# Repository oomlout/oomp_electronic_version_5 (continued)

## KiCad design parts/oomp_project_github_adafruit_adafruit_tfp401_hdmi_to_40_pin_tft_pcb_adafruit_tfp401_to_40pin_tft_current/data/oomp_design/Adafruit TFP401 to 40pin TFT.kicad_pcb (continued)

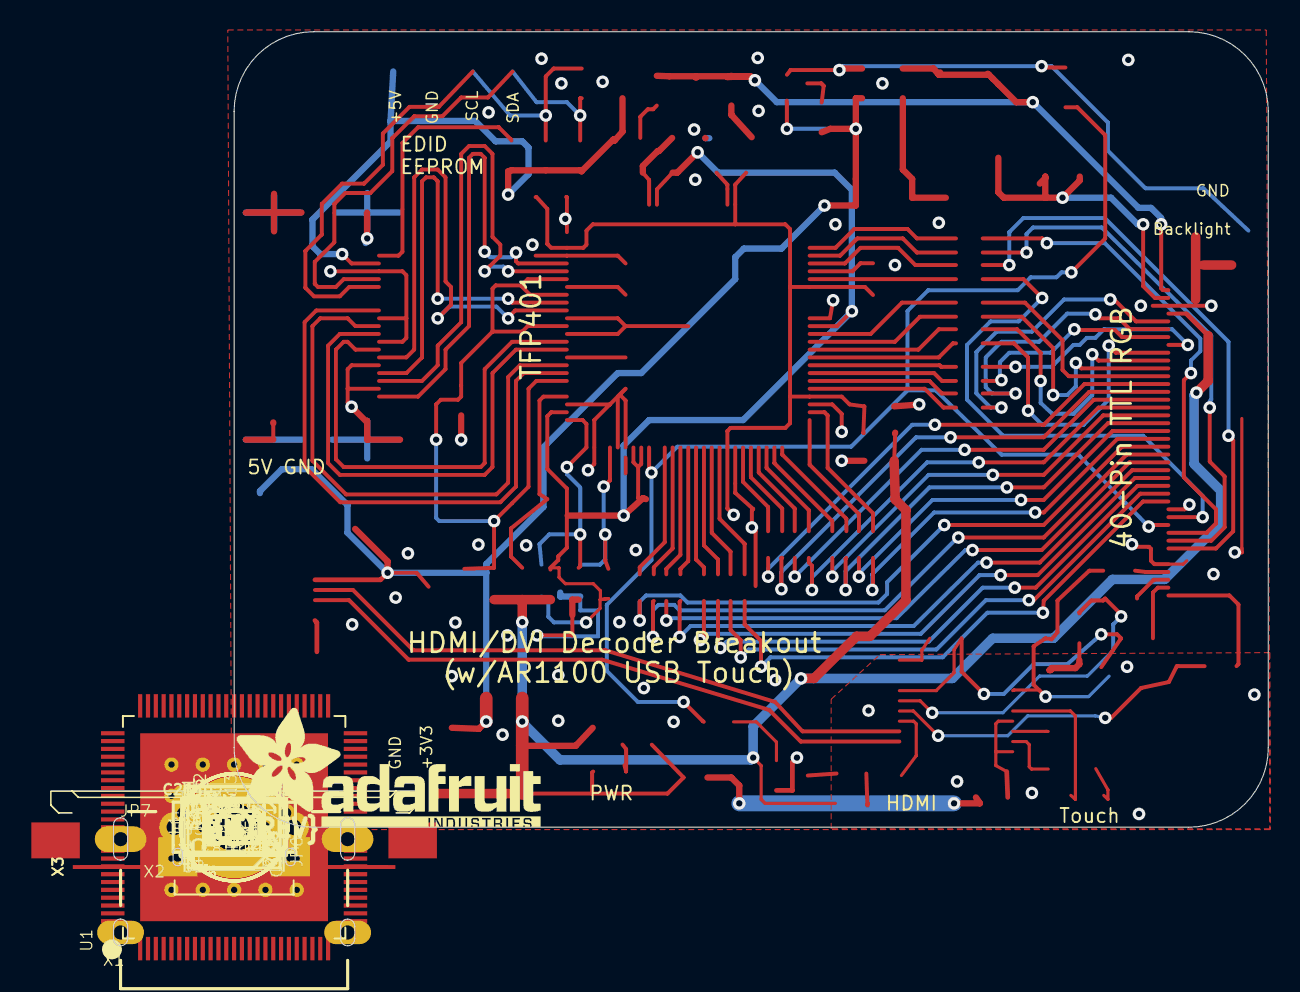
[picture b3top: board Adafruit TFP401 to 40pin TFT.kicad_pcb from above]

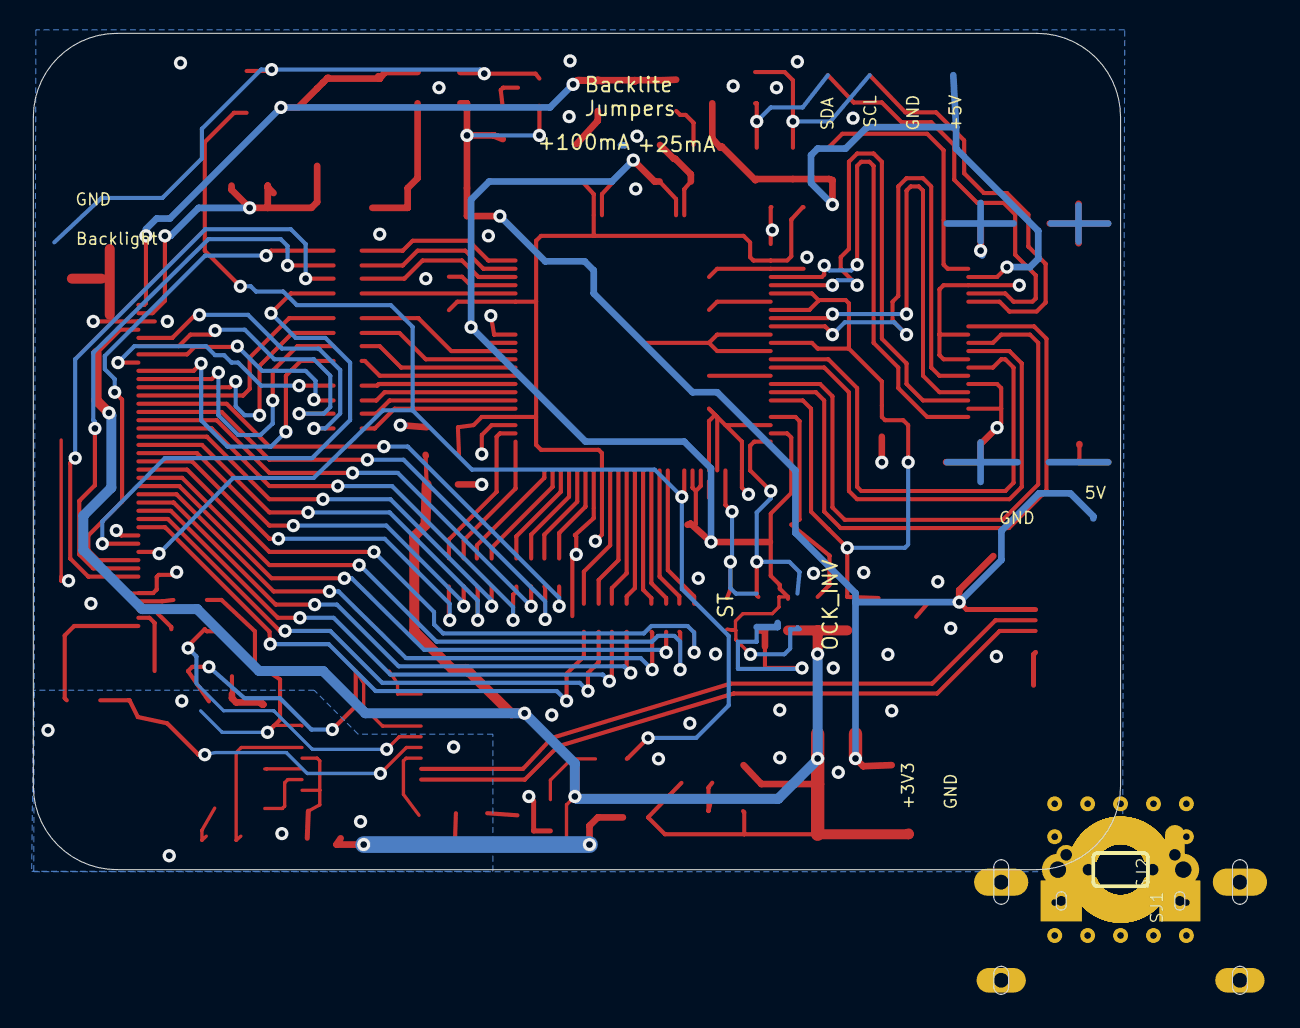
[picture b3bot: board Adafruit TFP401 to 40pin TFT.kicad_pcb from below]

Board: 2 copper layers, 66.0 x 50.8 mm, 92 parts (2 on the bottom side), 107 nets.

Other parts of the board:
U$80: PCBFEAT-REV-056
U$81: ADAFRUIT_TEXT_20MM

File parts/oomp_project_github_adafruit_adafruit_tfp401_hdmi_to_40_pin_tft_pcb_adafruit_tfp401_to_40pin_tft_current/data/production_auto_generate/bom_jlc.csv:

Comment,Designator,Footprint,LCSC Part #
,"JP1,JP2,JP6",Adafruit TFP401 to 40pin TFT-import-fps:1X02_ROUND,C492401
,JP7,Adafruit TFP401 to 40pin TFT-import-fps:1X04_ROUND_76,C42431795
,U$81,Adafruit TFP401 to 40pin TFT-import-fps:ADAFRUIT_TEXT_20MM,
,U$80,Adafruit TFP401 to 40pin TFT-import-fps:PCBFEAT-REV-056,
0.01uF,"C21,C22,C24,C25",Adafruit TFP401 to 40pin TFT-import-fps:0805-NO,
0.1uF,"C1,C2,C3,C4,C5,C7,C8,C9,C10,C11,C19,C20,C23",Adafruit TFP401 to 40pin TFT-import-fps:0805-NO,
0.1uF,C6,Adafruit TFP401 to 40pin TFT-import-fps:_0805MP,
100uF,C26,Adafruit TFP401 to 40pin TFT-import-fps:PANASONIC_C,
10K,"R1,R2,R3,R4,R18",Adafruit TFP401 to 40pin TFT-import-fps:0805-NO,C17414
10K,"R5,R13",Adafruit TFP401 to 40pin TFT-import-fps:_0805MP,C17414
10uF,"C12,C13,C14,C15,C16",Adafruit TFP401 to 40pin TFT-import-fps:0805-NO,
12 ohm,"R16,R17",Adafruit TFP401 to 40pin TFT-import-fps:0805-NO,C2907226
12MHz,Y1,Adafruit TFP401 to 40pin TFT-import-fps:RESONATOR-SMD,
1K,"R14,R19,R20,R21",Adafruit TFP401 to 40pin TFT-import-fps:0805-NO,C17513
1uF,"C17,C18",Adafruit TFP401 to 40pin TFT-import-fps:0805-NO,
24LC02BT-I/OT,U2,Adafruit TFP401 to 40pin TFT-import-fps:SOT23-5,
2N4148,D3,Adafruit TFP401 to 40pin TFT-import-fps:SOD-323,
3 ohm,R15,Adafruit TFP401 to 40pin TFT-import-fps:0805-NO,
33,"R6,R7,R8,R9,R10,R11,R12",Adafruit TFP401 to 40pin TFT-import-fps:RESPACK_4X0603,C23140
47151-0001,X1,Adafruit TFP401 to 40pin TFT-import-fps:HDMI_MOLEX_47151-0001_DIMLAYER,
AR1100_SSOP,IC1,Adafruit TFP401 to 40pin TFT-import-fps:TSSOP20-5.3MMBODY,
Blue,LED3,Adafruit TFP401 to 40pin TFT-import-fps:CHIPLED_0805_NOOUTLINE,
BRL3225T150K,L1,Adafruit TFP401 to 40pin TFT-import-fps:INDUCTOR_5X5MM_NR5040_NOTHERMALS,
BSS138,Q1,Adafruit TFP401 to 40pin TFT-import-fps:SOT23-R,C52895
FAN5333BSX,U4,Adafruit TFP401 to 40pin TFT-import-fps:SOT23-5,
Ferrite,"FB1,FB2,FB3,FB4,FB7,FB8",Adafruit TFP401 to 40pin TFT-import-fps:_0805MP,
ferrite,"FB5,FB6,FB9,FB10",Adafruit TFP401 to 40pin TFT-import-fps:_0805MP,
Green,LED2,Adafruit TFP401 to 40pin TFT-import-fps:CHIPLED_0805_NOOUTLINE,
LT1117(3V3),U3,Adafruit TFP401 to 40pin TFT-import-fps:SOT223-R,
MBR0540,D1,Adafruit TFP401 to 40pin TFT-import-fps:SOD-123,
microUSB,X2,Adafruit TFP401 to 40pin TFT-import-fps:4UCONN_20329,
MM3Z24VT1G,D2,Adafruit TFP401 to 40pin TFT-import-fps:SMADIODE,
Red,LED1,Adafruit TFP401 to 40pin TFT-import-fps:CHIPLED_0805_NOOUTLINE,
TFP401,U1,Adafruit TFP401 to 40pin TFT-import-fps:S-PQFP-G100,
XF2-40-RARBT,X3,Adafruit TFP401 to 40pin TFT-import-fps:4-1734839-0,

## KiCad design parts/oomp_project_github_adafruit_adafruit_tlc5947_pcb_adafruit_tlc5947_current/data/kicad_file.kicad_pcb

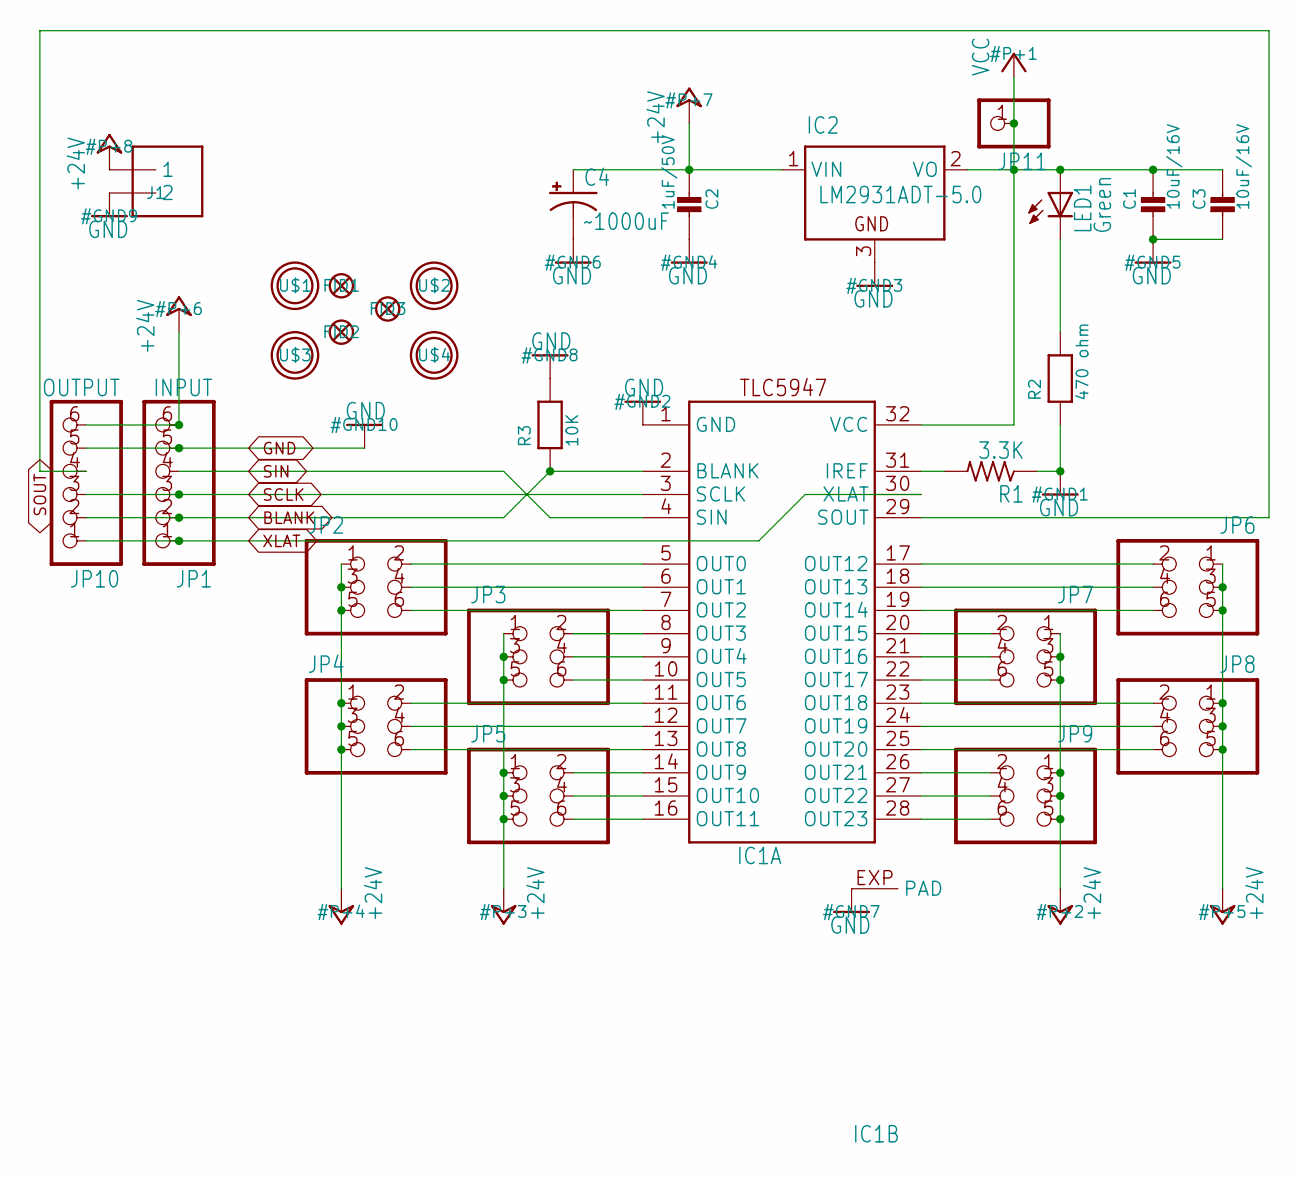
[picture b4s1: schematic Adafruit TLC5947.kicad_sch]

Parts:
C1, C3: 10uF/16V; 0805
C2: 1uF/50V; 0805
C4: ~1000uF; E3,5-8
FID1, FID2, FID3: FIDUCIAL""; FIDUCIAL_1MM
IC1: TLC5947-DAP; HTSSOP32DAP
IC2: LM2931ADT-5.0; TO252; MPN LM2936DT-3.3.
J1: 1X2-3.5MM
JP1: INPUT; 1X06-CLEANBIG
JP2, JP3, JP4, JP5, JP6, JP7, JP8, JP9: HEADER-2X3; 2X03_ROUND_70MIL
JP10: OUTPUT; 1X06-CLEANBIG
JP11: PINHD-1X1CB; 1X01-CLEANBIG
LED1: Green; CHIP-LED0805
R1: 3.3K; 0805-THM
R2: 470 ohm; 0805
R3: 10K; 0805
U$1, U$2, U$3, U$4: MOUNTINGHOLE2.5; MOUNTINGHOLE_2.5_PLATED

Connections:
+24V: C2.1, C4.+, IC2.1 (VIN), J1.1, JP1.6, JP2.1, JP2.3, JP2.5, JP3.1, JP3.3, JP3.5, JP4.1, JP4.3, JP4.5, JP5.1, JP5.3, JP5.5, JP6.1, JP6.3, JP6.5, JP7.1, JP7.3, JP7.5, JP8.1, JP8.3, JP8.5, JP9.1, JP9.3, JP9.5, JP10.6
BLANK: IC1.2 (BLANK), JP1.2, JP10.2, R3.1
GND: C1.2, C2.2, C3.2, C4.-, IC1.1 (GND), IC1.EXP (PAD), IC2.3 (GND), J1.2, JP1.5, JP10.5, R1.1, R2.1, R3.2
unnamed: LED1.C, R2.2
unnamed: IC1.31 (IREF), R1.2
unnamed: IC1.5 (OUT0), JP2.2
unnamed: IC1.6 (OUT1), JP2.4
unnamed: IC1.7 (OUT2), JP2.6
unnamed: IC1.8 (OUT3), JP3.2
unnamed: IC1.9 (OUT4), JP3.4
unnamed: IC1.10 (OUT5), JP3.6
unnamed: IC1.11 (OUT6), JP4.2
unnamed: IC1.12 (OUT7), JP4.4
unnamed: IC1.13 (OUT8), JP4.6
unnamed: IC1.14 (OUT9), JP5.2
unnamed: IC1.15 (OUT10), JP5.4
unnamed: IC1.16 (OUT11), JP5.6
unnamed: IC1.26 (OUT21), JP9.2
unnamed: IC1.27 (OUT22), JP9.4
unnamed: IC1.28 (OUT23), JP9.6
unnamed: IC1.23 (OUT18), JP8.2
unnamed: IC1.24 (OUT19), JP8.4
unnamed: IC1.25 (OUT20), JP8.6
unnamed: IC1.20 (OUT15), JP7.2
unnamed: IC1.21 (OUT16), JP7.4
unnamed: IC1.22 (OUT17), JP7.6
unnamed: IC1.17 (OUT12), JP6.2
unnamed: IC1.18 (OUT13), JP6.4
unnamed: IC1.19 (OUT14), JP6.6
SCLK: IC1.3 (SCLK), JP1.3, JP10.3
SIN: IC1.4 (SIN), JP1.4
SOUT: IC1.29 (SOUT), JP10.4
VCC: C1.1, C3.1, IC1.32 (VCC), IC2.2 (VO), JP11.1, LED1.A
XLAT: IC1.30 (XLAT), JP1.1, JP10.1

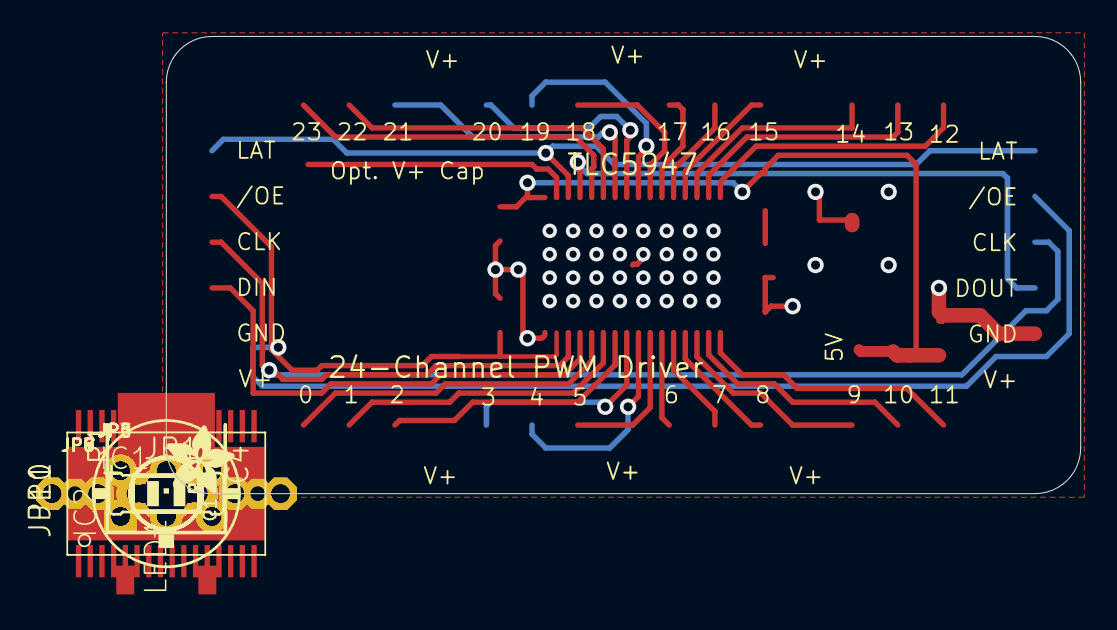
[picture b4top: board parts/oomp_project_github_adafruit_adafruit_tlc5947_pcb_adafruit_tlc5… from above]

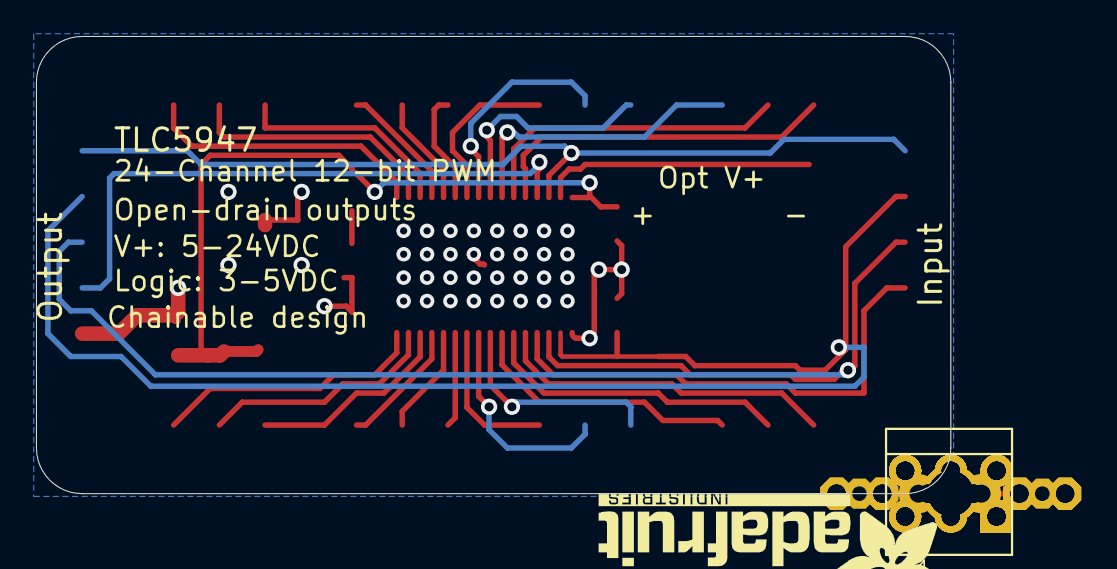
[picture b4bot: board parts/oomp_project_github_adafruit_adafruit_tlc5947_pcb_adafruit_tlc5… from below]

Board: 2 copper layers, 50.8 x 25.4 mm, 31 parts (2 on the bottom side), 34 nets.

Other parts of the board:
U$5: ADAFRUIT_TEXT_20MM
U$6: ADAFRUIT_3.5MM

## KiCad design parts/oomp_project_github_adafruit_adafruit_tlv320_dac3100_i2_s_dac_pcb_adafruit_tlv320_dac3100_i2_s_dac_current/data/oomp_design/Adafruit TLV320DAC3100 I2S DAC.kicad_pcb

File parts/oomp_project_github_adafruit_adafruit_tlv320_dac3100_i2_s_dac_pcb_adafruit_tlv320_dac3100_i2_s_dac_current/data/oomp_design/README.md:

# OOMP KiCad design copy

Open `Adafruit TLV320DAC3100 I2S DAC.kicad_pro` (or the `.kicad_pcb` / `.kicad_sch`) in KiCad. Local OOMP libraries are under `libraries/`. Original inputs are preserved in [../original/](../original/).

Only verified unchanged installed KiCad defaults were renamed. Modified, custom, unmatched and unavailable items remain unchanged. Soldering variants are never swapped during conversion. Existing pad coordinates, nets and UUIDs are preserved.

See [conversion_report.yaml](conversion_report.yaml) for every conversion and skip. Copy this directory before editing; regeneration refuses to overwrite edited design files.

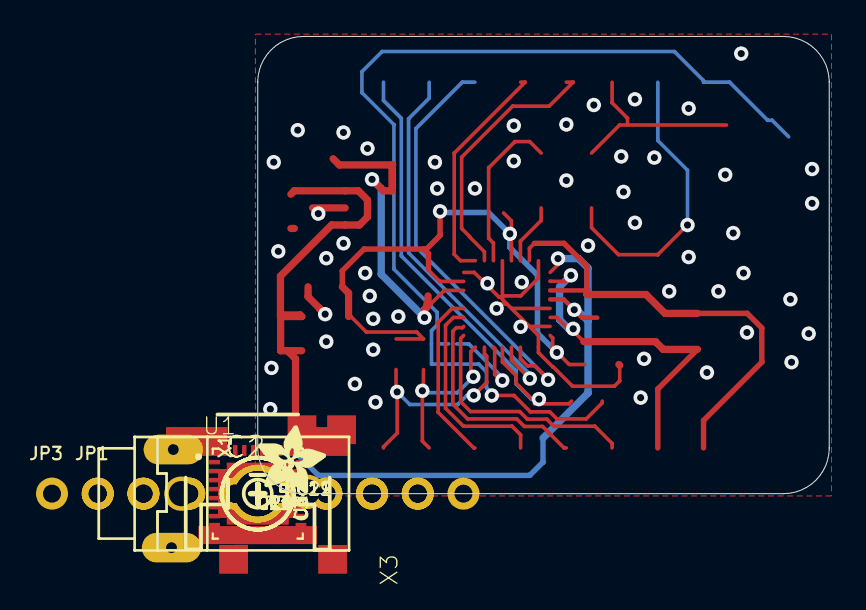
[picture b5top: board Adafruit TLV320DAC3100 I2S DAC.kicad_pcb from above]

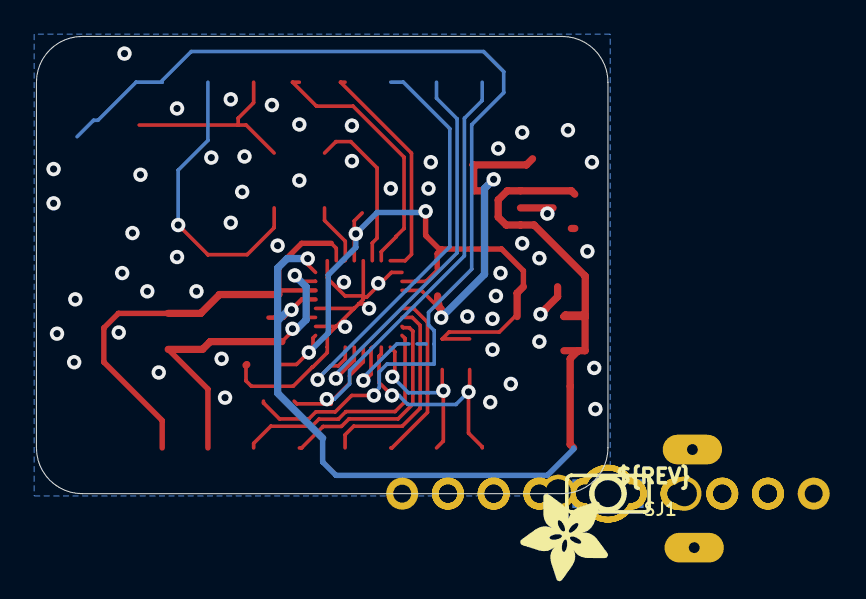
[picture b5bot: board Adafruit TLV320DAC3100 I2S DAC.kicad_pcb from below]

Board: 2 copper layers, 31.8 x 25.4 mm, 60 parts (10 on the bottom side), 23 nets.

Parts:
C1, C2: 100uF/6.3V; C1210
C3, C4, C11, C12, C19, C22: 10uF; 0805-NO
C15, C16, C20, C21: 0.1uF; 0603-NO
E$1: SYMBOL_MINUS
FID1, FID2: FIDUCIAL_0.5MM
JP1: 1X08_ROUND_70
JP3: 1X10_ROUND70
PLABEL0: PLABEL0
PLABEL1: PLABEL1
PLABEL2: PLABEL2
PLABEL3: PLABEL3
PLABEL4: PLABEL4
PLABEL5: PLABEL5
PLABEL6: PLABEL6
PLABEL7: PLABEL7
PLABEL8: PLABEL8
PLABEL9: PLABEL9
PLABEL10: PLABEL10
PLABEL11: PLABEL11
PLABEL12: PLABEL12
PLABEL13: PLABEL13
PLABEL14: PLABEL14
PLABEL15: PLABEL15
PLABEL16: PLABEL16
PLABEL17: PLABEL17
PLABEL18: PLABEL18
PLABEL19: PLABEL19
PLABEL20: PLABEL20
PLABEL21: PLABEL21
PLABEL22: PLABEL22
PLABEL23: PLABEL23
PLABEL24: PLABEL24
PLABEL25: PLABEL25
PLABEL26: PLABEL26
R1, R8, R9: 10k; 0603-NO
R3: 2.2K; 0603-NO
SJ1: SOLDERJUMPER_2WAY_OPEN_NOPASTE
U1: TLV320DAC3100
U2: AP2127K-3.3; SOT23-5
U3: AP2127K-1.8; SOT23-5
U$5: PCBFEAT-REV-040
U$6: ADAFRUIT_5MM
U$12, U$13, U$14: MOUNTINGHOLE2.5; MOUNTINGHOLE_2.5_PLATED
U$29: ADAFRUIT_3.5MM
X1: CON_JST_PH_2PIN_MTPH2; JSTPH2
X3: TRRS_2SWITCH_PJ332A; PJ-332A

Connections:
1.8V: C4.1, C15.1, C16.1, U1.3, U3.5
3.3V: C12.1, C20.1, C21.1, C22.1, R1.2, R8.2, R9.2, U1.2, U1.17, U1.28, U2.5
AGND: C3.2, C4.2, C11.2, C12.2, C15.2, C16.2, C19.2, C20.2, C21.2, C22.2, JP3.2, SJ1.3, U1.1, U1.16, U1.18, U1.20, U1.25, U1.29, U1.33, U2.2, U3.2, X1.NC1, X1.NC2, X3.2
AIN1: JP1.2, U1.13
AIN2: JP1.3, U1.14
BITCLK_IN: JP3.7, U1.7
DATA_IN: JP3.5, U1.5
GPIO1: JP1.4, U1.32
HPL: C1.1, U1.27
HPR: C2.1, U1.30
MCLK: JP3.8, U1.8
MIC: JP1.8, R3.1, SJ1.2, X3.1
MICBIAS: JP1.1, R3.2, U1.12
MICDET: SJ1.1, U1.11
OUTL: C1.2, JP1.7, X3.4, X3.6
OUTR: C2.2, JP1.6, X3.3, X3.5
SCL: JP3.3, R9.1, U1.10
SDA: JP3.4, R8.1, U1.9
SPKM: JP3.9, U1.19, U1.23, X1.2
SPKP: JP3.10, U1.22, U1.26, X1.1
VIN: C3.1, C11.1, C19.1, JP3.1, U1.21, U1.24, U2.1, U2.3, U3.1, U3.3
WORDSEL_IN: JP3.6, U1.6
~RESET: JP1.5, R1.1, U1.31

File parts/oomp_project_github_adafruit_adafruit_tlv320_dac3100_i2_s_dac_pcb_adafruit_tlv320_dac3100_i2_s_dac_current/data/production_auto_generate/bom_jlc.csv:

Comment,Designator,Footprint,LCSC Part #
,JP1,Adafruit TLV320DAC3100 I2S DAC-import-fps:1X08_ROUND_70,C492421
,JP3,Adafruit TLV320DAC3100 I2S DAC-import-fps:1X10_ROUND70,C57369
,U$29,Adafruit TLV320DAC3100 I2S DAC-import-fps:ADAFRUIT_3.5MM,
,U$6,Adafruit TLV320DAC3100 I2S DAC-import-fps:ADAFRUIT_5MM,
,U$5,Adafruit TLV320DAC3100 I2S DAC-import-fps:PCBFEAT-REV-040,
,PLABEL0,Adafruit TLV320DAC3100 I2S DAC-import-fps:PLABEL0,
,PLABEL1,Adafruit TLV320DAC3100 I2S DAC-import-fps:PLABEL1,
,PLABEL10,Adafruit TLV320DAC3100 I2S DAC-import-fps:PLABEL10,
,PLABEL11,Adafruit TLV320DAC3100 I2S DAC-import-fps:PLABEL11,
,PLABEL12,Adafruit TLV320DAC3100 I2S DAC-import-fps:PLABEL12,
,PLABEL13,Adafruit TLV320DAC3100 I2S DAC-import-fps:PLABEL13,
,PLABEL14,Adafruit TLV320DAC3100 I2S DAC-import-fps:PLABEL14,
,PLABEL15,Adafruit TLV320DAC3100 I2S DAC-import-fps:PLABEL15,
,PLABEL16,Adafruit TLV320DAC3100 I2S DAC-import-fps:PLABEL16,
,PLABEL17,Adafruit TLV320DAC3100 I2S DAC-import-fps:PLABEL17,
,PLABEL18,Adafruit TLV320DAC3100 I2S DAC-import-fps:PLABEL18,
,PLABEL19,Adafruit TLV320DAC3100 I2S DAC-import-fps:PLABEL19,
,PLABEL2,Adafruit TLV320DAC3100 I2S DAC-import-fps:PLABEL2,
,PLABEL20,Adafruit TLV320DAC3100 I2S DAC-import-fps:PLABEL20,
,PLABEL21,Adafruit TLV320DAC3100 I2S DAC-import-fps:PLABEL21,
,PLABEL22,Adafruit TLV320DAC3100 I2S DAC-import-fps:PLABEL22,
,PLABEL23,Adafruit TLV320DAC3100 I2S DAC-import-fps:PLABEL23,
,PLABEL24,Adafruit TLV320DAC3100 I2S DAC-import-fps:PLABEL24,
,PLABEL25,Adafruit TLV320DAC3100 I2S DAC-import-fps:PLABEL25,
,PLABEL26,Adafruit TLV320DAC3100 I2S DAC-import-fps:PLABEL26,
,PLABEL3,Adafruit TLV320DAC3100 I2S DAC-import-fps:PLABEL3,
,PLABEL4,Adafruit TLV320DAC3100 I2S DAC-import-fps:PLABEL4,
,PLABEL5,Adafruit TLV320DAC3100 I2S DAC-import-fps:PLABEL5,
,PLABEL6,Adafruit TLV320DAC3100 I2S DAC-import-fps:PLABEL6,
,PLABEL7,Adafruit TLV320DAC3100 I2S DAC-import-fps:PLABEL7,
,PLABEL8,Adafruit TLV320DAC3100 I2S DAC-import-fps:PLABEL8,
,PLABEL9,Adafruit TLV320DAC3100 I2S DAC-import-fps:PLABEL9,
,E$1,Adafruit TLV320DAC3100 I2S DAC-import-fps:SYMBOL_MINUS,
0.1uF,"C15,C16,C20,C21",Adafruit TLV320DAC3100 I2S DAC-import-fps:0603-NO,C14663
100uF/6.3V,"C1,C2",Adafruit TLV320DAC3100 I2S DAC-import-fps:C1210,
10k,"R1,R8,R9",Adafruit TLV320DAC3100 I2S DAC-import-fps:0603-NO,C98220
10uF,"C3,C4,C11,C12,C19,C22",Adafruit TLV320DAC3100 I2S DAC-import-fps:0805-NO,
2.2K,R3,Adafruit TLV320DAC3100 I2S DAC-import-fps:0603-NO,C4190
AP2127K-1.8,U3,Adafruit TLV320DAC3100 I2S DAC-import-fps:SOT23-5,
AP2127K-3.3,U2,Adafruit TLV320DAC3100 I2S DAC-import-fps:SOT23-5,
CON_JST_PH_2PIN_MTPH2,X1,Adafruit TLV320DAC3100 I2S DAC-import-fps:JSTPH2,
TLV320DAC3100,U1,Adafruit TLV320DAC3100 I2S DAC-import-fps:TLV320DAC3100,
TRRS_2SWITCH_PJ332A,X3,Adafruit TLV320DAC3100 I2S DAC-import-fps:PJ-332A,
